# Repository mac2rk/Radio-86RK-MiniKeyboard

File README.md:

# Mini Keyboard for Radio-86RK

A mini keyboard for Radio-86RK, a 1986 DIY 8-bit home computer.

## Introduction

When I designed my [Radio-86RK-SRAM](https://github.com/mac2rk/Radio-86RK-SRAM) remake of the 1986 DIY 8-bit home computer, I built in a PS/2 keyboard adapter to stay away from homebrew keyboards and use a commercial full-size keyboard instead. I found, however, that in many cases the full size keyboard took too much space, so I designed a mini matrix keyboard built from tact momentary switches. The design was inspired by the [Hackaday Belgrade 2018 conference badge](https://hackaday.com/2018/05/15/retro-computer-badge-for-hackaday-belgrade-has-everything-you-wished-for-back-in-the-day/).

Due to the large number of SMT tact buttons, it is easier to solder in an SMT over or with hot air. Normal manual soldering is quite possible, too.

## Schematic and PCB layout
[Schematic](Eagle/rk86-kbd-schematic.pdf)

[PCB layout](Eagle/rk86-kbd-silk.pdf)

## Bill of Materials

Device                | Package   | Quantity
--------------------- | --------- | -------
Tact momentary switch | 6x6mm SMT | 67
Resistor 2kOhm        | 0805      | 11
Resistor 330Ohm       | 0805      | 2
1N4148W diode         | SOD-123   | 8
LED                   | 0805      | 2
2x13 box header       | Right Angle | 1

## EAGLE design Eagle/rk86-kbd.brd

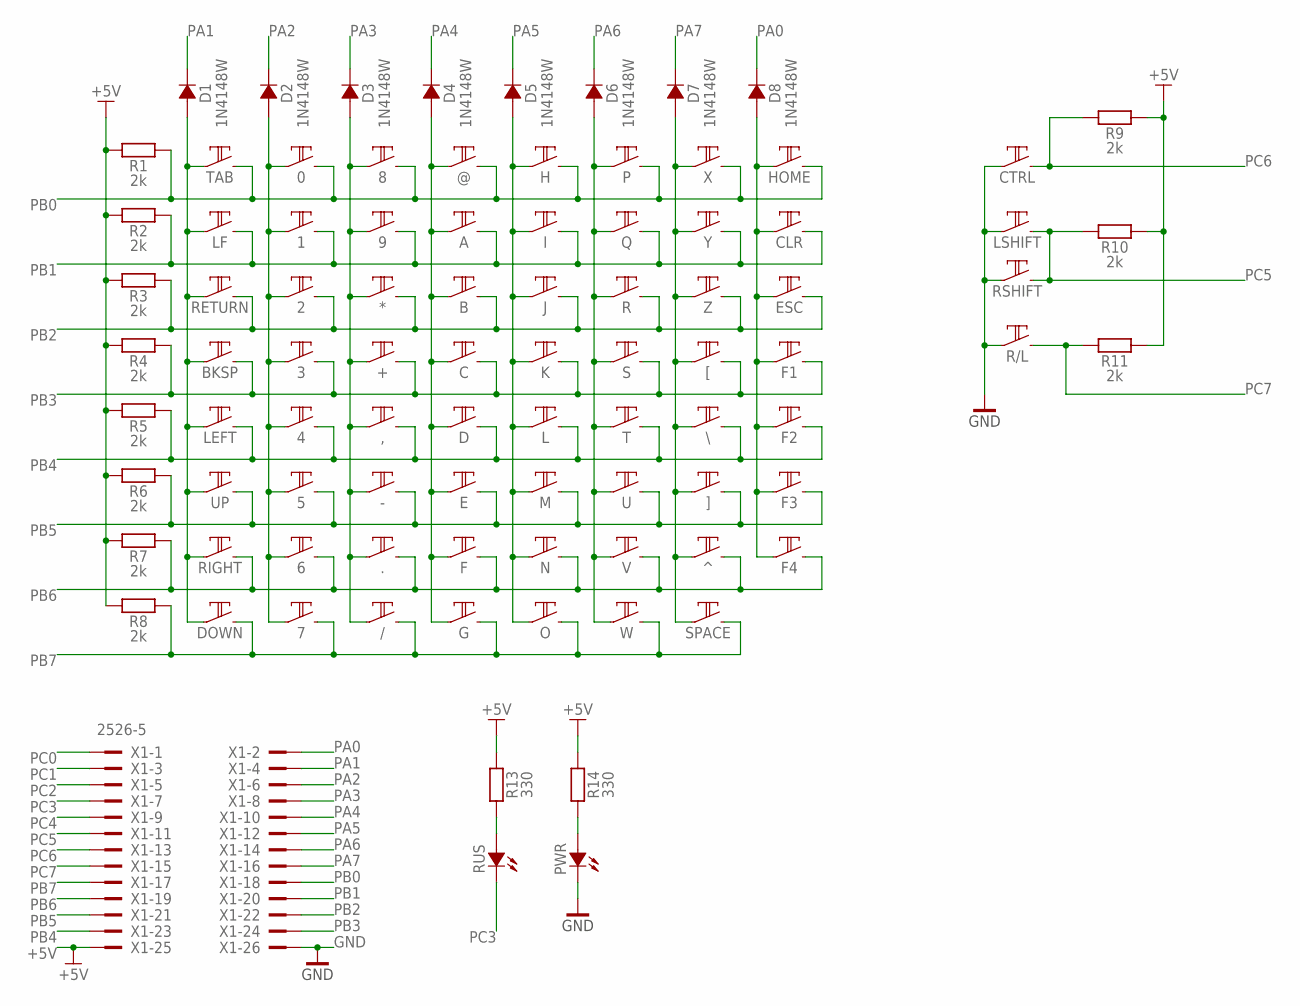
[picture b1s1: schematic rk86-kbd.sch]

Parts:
0, 1, 2, 3, 4, 5, 6, 7, 8, 9, .: TACT6S-15; TACT_6X6_SMT_15
*: TACT6S-15; TACT_6X6_SMT_15
+: TACT6S-15; TACT_6X6_SMT_15
,: TACT6S-15; TACT_6X6_SMT_15
-: TACT6S-15; TACT_6X6_SMT_15
/: TACT6S-15; TACT_6X6_SMT_15
@: TACT6S-15; TACT_6X6_SMT_15
A: TACT6S-15; TACT_6X6_SMT_15
B: TACT6S-15; TACT_6X6_SMT_15
BKSP: TACT6S-15; TACT_6X6_SMT_15
C: TACT6S-15; TACT_6X6_SMT_15
CLR: TACT6S-15; TACT_6X6_SMT_15
CTRL: TACT6S-15; TACT_6X6_SMT_15
D: TACT6S-15; TACT_6X6_SMT_15
D1, D2, D3, D4, D5, D6, D7, D8: 1N4148W; SOD123
DOWN: TACT6S-15; TACT_6X6_SMT_15
E: TACT6S-15; TACT_6X6_SMT_15
ESC: TACT6S-15; TACT_6X6_SMT_15
F, F1, F2, F3, F4: TACT6S-15; TACT_6X6_SMT_15
G: TACT6S-15; TACT_6X6_SMT_15
H: TACT6S-15; TACT_6X6_SMT_15
HOME: TACT6S-15; TACT_6X6_SMT_15
I: TACT6S-15; TACT_6X6_SMT_15
J: TACT6S-15; TACT_6X6_SMT_15
K: TACT6S-15; TACT_6X6_SMT_15
L: TACT6S-15; TACT_6X6_SMT_15
LEFT: TACT6S-15; TACT_6X6_SMT_15
LF: TACT6S-15; TACT_6X6_SMT_15
LSHIFT: TACT6S-15; TACT_6X6_SMT_15
M: TACT6S-15; TACT_6X6_SMT_15
N: TACT6S-15; TACT_6X6_SMT_15
O: TACT6S-15; TACT_6X6_SMT_15
P: TACT6S-15; TACT_6X6_SMT_15
PWR: LED0805; 0805POL
Q: TACT6S-15; TACT_6X6_SMT_15
R: TACT6S-15; TACT_6X6_SMT_15
R1, R2, R3, R4, R5, R6, R7, R8, R9, R10, R11: 2k; 0805
R13, R14: 330; 0805
R/L: TACT6S-15; TACT_6X6_SMT_15
RETURN: TACT6S-15; TACT_6X6_SMT_15
RIGHT: TACT6S-15; TACT_6X6_SMT_15
RSHIFT: TACT6S-15; TACT_6X6_SMT_15
RUS: LED0805; 0805POL
S: TACT6S-15; TACT_6X6_SMT_15
SPACE: TACT6S-15; TACT_6X6_SMT_15
T: TACT6S-15; TACT_6X6_SMT_15
TAB: TACT6S-15; TACT_6X6_SMT_15
U: TACT6S-15; TACT_6X6_SMT_15
UP: TACT6S-15; TACT_6X6_SMT_15
V: TACT6S-15; TACT_6X6_SMT_15
W: TACT6S-15; TACT_6X6_SMT_15
X: TACT6S-15; TACT_6X6_SMT_15
X1: 2526-5; PAK100/2500-5-26
Y: TACT6S-15; TACT_6X6_SMT_15
Z: TACT6S-15; TACT_6X6_SMT_15
[: TACT6S-15; TACT_6X6_SMT_15
\\: TACT6S-15; TACT_6X6_SMT_15
]: TACT6S-15; TACT_6X6_SMT_15
^: TACT6S-15; TACT_6X6_SMT_15

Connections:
+5V: R1.1, R2.1, R3.1, R4.1, R5.1, R6.1, R7.1, R8.1, R9.2, R10.2, R11.2, R13.2, R14.2, X1.25
GND: CTRL.1 (C), CTRL.2 (C), LSHIFT.1 (C), LSHIFT.2 (C), PWR.K, R/L.1 (C), R/L.2 (C), RSHIFT.1 (C), RSHIFT.2 (C), X1.26
unnamed: R13.1, RUS.A
unnamed: PWR.A, R14.1
PA0: D8.K, X1.2
PA0D: CLR.1 (C), CLR.2 (C), D8.A, ESC.1 (C), ESC.2 (C), F1.1 (C), F1.2 (C), F2.1 (C), F2.2 (C), F3.1 (C), F3.2 (C), F4.1 (C), F4.2 (C), HOME.1 (C), HOME.2 (C)
PA1: D1.K, X1.4
PA1D: BKSP.1 (C), BKSP.2 (C), D1.A, DOWN.1 (C), DOWN.2 (C), LEFT.1 (C), LEFT.2 (C), LF.1 (C), LF.2 (C), RETURN.1 (C), RETURN.2 (C), RIGHT.1 (C), RIGHT.2 (C), TAB.1 (C), TAB.2 (C), UP.1 (C), UP.2 (C)
PA2: D2.K, X1.6
PA2D: 0.1 (C), 0.2 (C), 1.1 (C), 1.2 (C), 2.1 (C), 2.2 (C), 3.1 (C), 3.2 (C), 4.1 (C), 4.2 (C), 5.1 (C), 5.2 (C), 6.1 (C), 6.2 (C), 7.1 (C), 7.2 (C), D2.A
PA3: D3.K, X1.8
PA3D: 8.1 (C), 8.2 (C), 9.1 (C), 9.2 (C), *.1 (C), *.2 (C), +.1 (C), +.2 (C), ,.1 (C), ,.2 (C), -.1 (C), -.2 (C), ..1 (C), ..2 (C), /.1 (C), /.2 (C), D3.A
PA4: D4.K, X1.10
PA4D: @.1 (C), @.2 (C), A.1 (C), A.2 (C), B.1 (C), B.2 (C), C.1 (C), C.2 (C), D.1 (C), D.2 (C), D4.A, E.1 (C), E.2 (C), F.1 (C), F.2 (C), G.1 (C), G.2 (C)
PA5: D5.K, X1.12
PA5D: D5.A, H.1 (C), H.2 (C), I.1 (C), I.2 (C), J.1 (C), J.2 (C), K.1 (C), K.2 (C), L.1 (C), L.2 (C), M.1 (C), M.2 (C), N.1 (C), N.2 (C), O.1 (C), O.2 (C)
PA6: D6.K, X1.14
PA6D: D6.A, P.1 (C), P.2 (C), Q.1 (C), Q.2 (C), R.1 (C), R.2 (C), S.1 (C), S.2 (C), T.1 (C), T.2 (C), U.1 (C), U.2 (C), V.1 (C), V.2 (C), W.1 (C), W.2 (C)
PA7: D7.K, X1.16
PA7D: D7.A, SPACE.1 (C), SPACE.2 (C), X.1 (C), X.2 (C), Y.1 (C), Y.2 (C), Z.1 (C), Z.2 (C), [.1 (C), [.2 (C), \\.1 (C), \\.2 (C), ].1 (C), ].2 (C), ^.1 (C), ^.2 (C)
PB0: 0.3 (NO), 0.4 (NO), 8.3 (NO), 8.4 (NO), @.3 (NO), @.4 (NO), H.3 (NO), H.4 (NO), HOME.3 (NO), HOME.4 (NO), P.3 (NO), P.4 (NO), R1.2, TAB.3 (NO), TAB.4 (NO), X.3 (NO), X.4 (NO), X1.18
PB1: 1.3 (NO), 1.4 (NO), 9.3 (NO), 9.4 (NO), A.3 (NO), A.4 (NO), CLR.3 (NO), CLR.4 (NO), I.3 (NO), I.4 (NO), LF.3 (NO), LF.4 (NO), Q.3 (NO), Q.4 (NO), R2.2, X1.20, Y.3 (NO), Y.4 (NO)
PB2: 2.3 (NO), 2.4 (NO), *.3 (NO), *.4 (NO), B.3 (NO), B.4 (NO), ESC.3 (NO), ESC.4 (NO), J.3 (NO), J.4 (NO), R.3 (NO), R.4 (NO), R3.2, RETURN.3 (NO), RETURN.4 (NO), X1.22, Z.3 (NO), Z.4 (NO)
PB3: 3.3 (NO), 3.4 (NO), +.3 (NO), +.4 (NO), BKSP.3 (NO), BKSP.4 (NO), C.3 (NO), C.4 (NO), F1.3 (NO), F1.4 (NO), K.3 (NO), K.4 (NO), R4.2, S.3 (NO), S.4 (NO), X1.24, [.3 (NO), [.4 (NO)
PB4: 4.3 (NO), 4.4 (NO), ,.3 (NO), ,.4 (NO), D.3 (NO), D.4 (NO), F2.3 (NO), F2.4 (NO), L.3 (NO), L.4 (NO), LEFT.3 (NO), LEFT.4 (NO), R5.2, T.3 (NO), T.4 (NO), X1.23, \\.3 (NO), \\.4 (NO)
PB5: 5.3 (NO), 5.4 (NO), -.3 (NO), -.4 (NO), E.3 (NO), E.4 (NO), F3.3 (NO), F3.4 (NO), M.3 (NO), M.4 (NO), R6.2, U.3 (NO), U.4 (NO), UP.3 (NO), UP.4 (NO), X1.21, ].3 (NO), ].4 (NO)
PB6: 6.3 (NO), 6.4 (NO), ..3 (NO), ..4 (NO), F.3 (NO), F.4 (NO), F4.3 (NO), F4.4 (NO), N.3 (NO), N.4 (NO), R7.2, RIGHT.3 (NO), RIGHT.4 (NO), V.3 (NO), V.4 (NO), X1.19, ^.3 (NO), ^.4 (NO)
PB7: 7.3 (NO), 7.4 (NO), /.3 (NO), /.4 (NO), DOWN.3 (NO), DOWN.4 (NO), G.3 (NO), G.4 (NO), O.3 (NO), O.4 (NO), R8.2, SPACE.3 (NO), SPACE.4 (NO), W.3 (NO), W.4 (NO), X1.17
PC0: X1.1
PC1: X1.3
PC2: X1.5
PC3: RUS.K, X1.7
PC4: X1.9
PC5: LSHIFT.3 (NO), LSHIFT.4 (NO), R10.1, RSHIFT.3 (NO), RSHIFT.4 (NO), X1.11
PC6: CTRL.3 (NO), CTRL.4 (NO), R9.1, X1.13
PC7: R11.1, R/L.3 (NO), R/L.4 (NO), X1.15

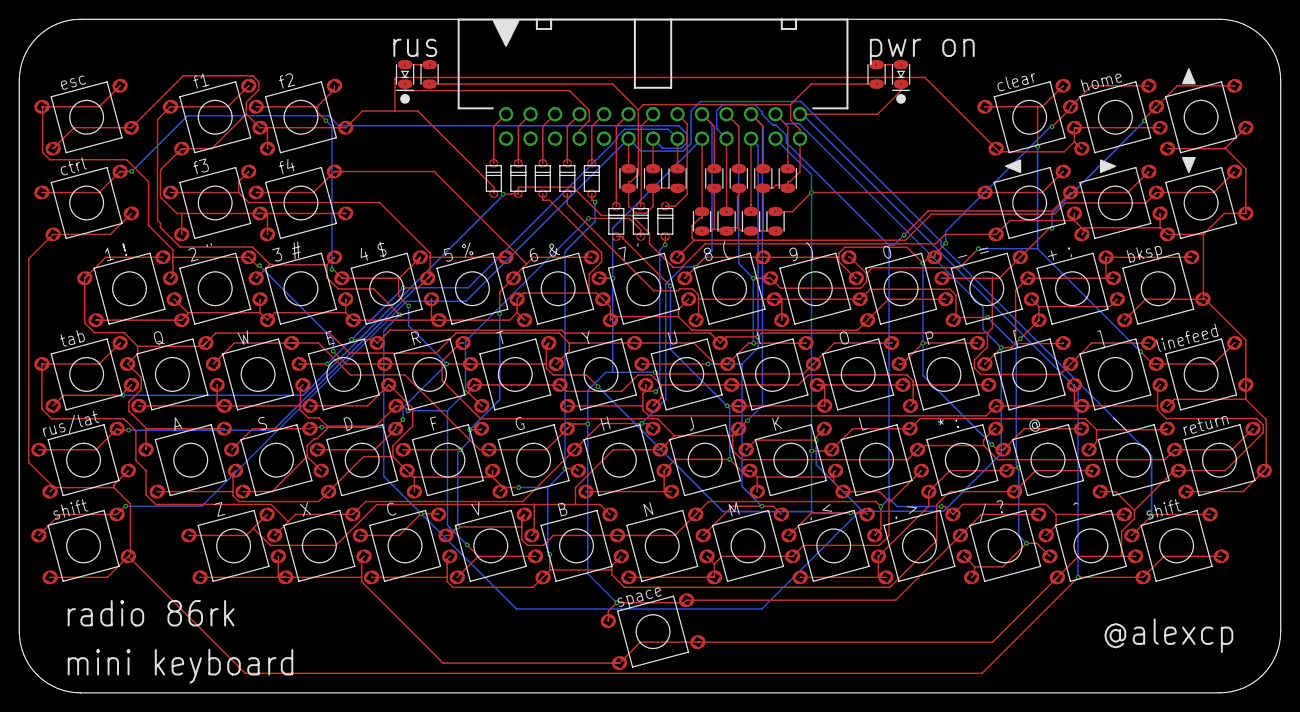
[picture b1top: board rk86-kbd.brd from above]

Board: 2 copper layers, 130.8 x 69.8 mm, 91 parts (0 on the bottom side), 32 nets.
